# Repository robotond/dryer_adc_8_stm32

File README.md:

# dryer_adc_8_stm32
Dryer 8 input ADC board based on STM31G070CBT6

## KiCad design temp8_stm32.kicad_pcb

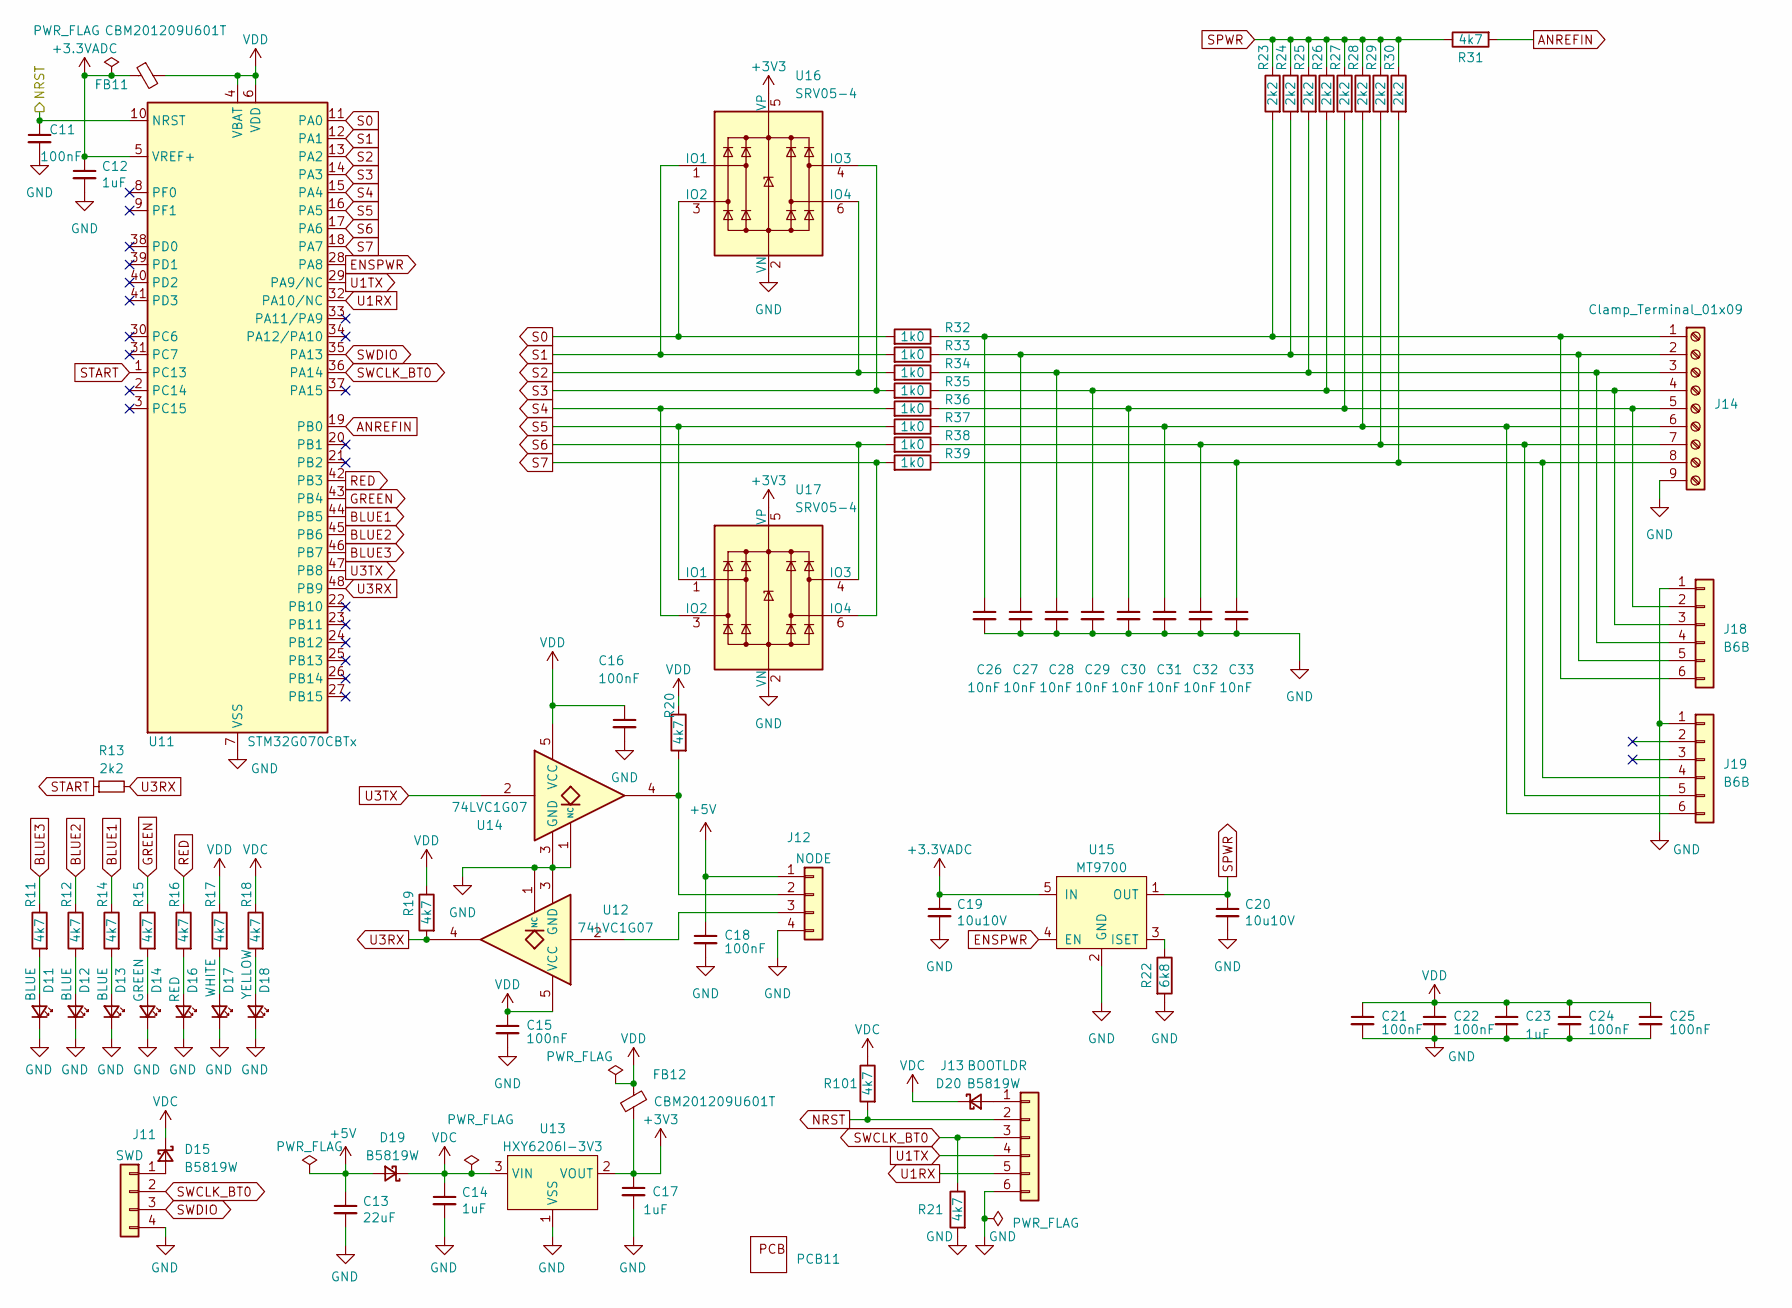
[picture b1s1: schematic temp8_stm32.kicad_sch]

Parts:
C11, C15, C16, C18, C21, C22, C24, C25: 100nF; C_0402_1005Metric; LCSC C1525
C12, C14, C17, C23: 1uF; C_0603_1608Metric; LCSC C15849
C13: 22uF; C_1206_3216Metric; LCSC C5672
C19, C20: 10u10V; C_0603_1608Metric; LCSC C19702
C26, C27, C28, C29, C30, C31, C32, C33: 10nF; C_0402_1005Metric; LCSC C15195
D11, D12, D13: BLUE; LED_0603_1608Metric; LCSC C72041
D14: GREEN; LED_0603_1608Metric; LCSC C72043
D15, D19, D20: B5819W; D_SOD-123; LCSC C8598
D16: RED; LED_0603_1608Metric; LCSC C2286
D17: WHITE; LED_0603_1608Metric; LCSC C2290
D18: YELLOW; LED_0603_1608Metric; LCSC C72038
FB11, FB12: CBM201209U601T; L_0805_2012Metric_Pad1.15x1.40mm_HandSolder; LCSC C139168
J11: SWD; JST_XH_B4B-XH-A_1x04_P2.50mm_Vertical; LCSC C144395
J12: NODE; JST_XH_B4B-XH-A_1x04_P2.50mm_Vertical; LCSC C144395
J13: BOOTLDR; JST_XH_B6B-XH-A_1x06_P2.50mm_Vertical; LCSC C144397
J14: Clamp_Terminal_01x09; DB141V-2.54-09P-C; LCSC C2898761
J18, J19: B6B; JST_XH_B6B-XH-A_1x06_P2.50mm_Vertical; LCSC C144397
PCB11: Dyer_ADC_78x28
R11, R12, R14, R15, R16, R17, R18, R19, R20, R21, R31, R101: 4k7; R_0402_1005Metric; LCSC C25900
R13, R23, R24, R25, R26, R27, R28, R29, R30: 2k2; R_0402_1005Metric; LCSC C517529
R22: 6k8; R_0402_1005Metric; LCSC C25917
R32, R33, R34, R35, R36, R37, R38, R39: 1k0; R_0402_1005Metric; LCSC C11702
U11: STM32G070CBTx; LQFP-48_7x7mm_P0.5mm; LCSC C529338
U12, U14: 74LVC1G07; SOT-23-5; LCSC C5124976
U13: HXY6206I-3V3; SOT-23; LCSC C5148688
U15: MT9700; SOT-23-5; LCSC C89855
U16, U17: SRV05-4; SOT-23-6; LCSC C2836319

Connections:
+3.3VADC: C12.1, C19.1, FB11.1, U11.5 (VREF+), U15.5 (IN)
+3V3: C17.1, FB12.2, U13.2 (VOUT), U16.5 (VP), U17.5 (VP)
+5V: C13.1, C18.1, D19.2 (A), J12.1
ANREFIN: R31.2, U11.19 (PB0)
BLUE1: R14.1, U11.44 (PB5)
BLUE2: R12.1, U11.45 (PB6)
BLUE3: R11.1, U11.46 (PB7)
ENSPWR: U11.28 (PA8), U15.4 (EN)
GND: C11.2, C12.2, C13.2, C14.2, C15.2, C16.2, C17.2, C18.2, C19.2, C20.2, C21.2, C22.2, C23.2, C24.2, C25.2, C26.2, C27.2, C28.2, C29.2, C30.2, C31.2, C32.2, C33.2, D11.1 (K), D12.1 (K), D13.1 (K), D14.1 (K), D16.1 (K), D17.1 (K), D18.1 (K), J11.4, J12.4, J13.6, J14.9, J18.1, J19.1, R21.2, R22.2, U11.7 (VSS), U12.1 (NC), U12.3 (GND), U13.1 (VSS), U14.1 (NC), U14.3 (GND), U15.2 (GND), U16.2 (VN), U17.2 (VN)
GREEN: R15.1, U11.43 (PB4)
NRST: C11.1, J13.2, R101.2, U11.10 (NRST)
unnamed: D11.2 (A), R11.2
unnamed: D12.2 (A), R12.2
unnamed: D13.2 (A), R14.2
unnamed: D14.2 (A), R15.2
unnamed: D15.2 (A), J11.1
unnamed: D16.2 (A), R16.2
unnamed: D17.2 (A), R17.2
unnamed: D18.2 (A), R18.2
unnamed: D20.2 (A), J13.1
unnamed: J12.2, R20.2, U14.4
unnamed: J12.3, U12.2
unnamed: C26.1, J14.1, J18.6, R23.2, R32.1
unnamed: C27.1, J14.2, J18.5, R24.2, R33.1
unnamed: C28.1, J14.3, J18.4, R25.2, R34.1
unnamed: C29.1, J14.4, J18.3, R26.2, R35.1
unnamed: C30.1, J14.5, J18.2, R27.2, R36.1
unnamed: C31.1, J14.6, J19.6, R28.2, R37.1
unnamed: C32.1, J14.7, J19.5, R29.2, R38.1
unnamed: C33.1, J14.8, J19.4, R30.2, R39.1
unnamed: R22.1, U15.3 (ISET)
RED: R16.1, U11.42 (PB3)
S0: R32.2, U11.11 (PA0), U16.3 (IO2)
S1: R33.2, U11.12 (PA1), U16.1 (IO1)
S2: R34.2, U11.13 (PA2), U16.6 (IO4)
S3: R35.2, U11.14 (PA3), U16.4 (IO3)
S4: R36.2, U11.15 (PA4), U17.3 (IO2)
S5: R37.2, U11.16 (PA5), U17.1 (IO1)
S6: R38.2, U11.17 (PA6), U17.4 (IO3)
S7: R39.2, U11.18 (PA7), U17.6 (IO4)
SPWR: C20.1, R23.1, R24.1, R25.1, R26.1, R27.1, R28.1, R29.1, R30.1, R31.1, U15.1 (OUT)
START: R13.1, U11.1 (PC13)
SWCLK_BT0: J11.2, J13.3, R21.1, U11.36 (PA14)
SWDIO: J11.3, U11.35 (PA13)
U1RX: J13.5, U11.32 (PA10/NC)
U1TX: J13.4, U11.29 (PA9/NC)
U3RX: R13.2, R19.2, U11.48 (PB9), U12.4
U3TX: U11.47 (PB8), U14.2
VDC: C14.1, D15.1 (K), D19.1 (K), D20.1 (K), R18.1, R101.1, U13.3 (VIN)
VDD: C15.1, C16.1, C21.1, C22.1, C23.1, C24.1, C25.1, FB11.2, FB12.1, R17.1, R19.1, R20.1, U11.4 (VBAT), U11.6 (VDD), U12.5 (VCC), U14.5 (VCC)

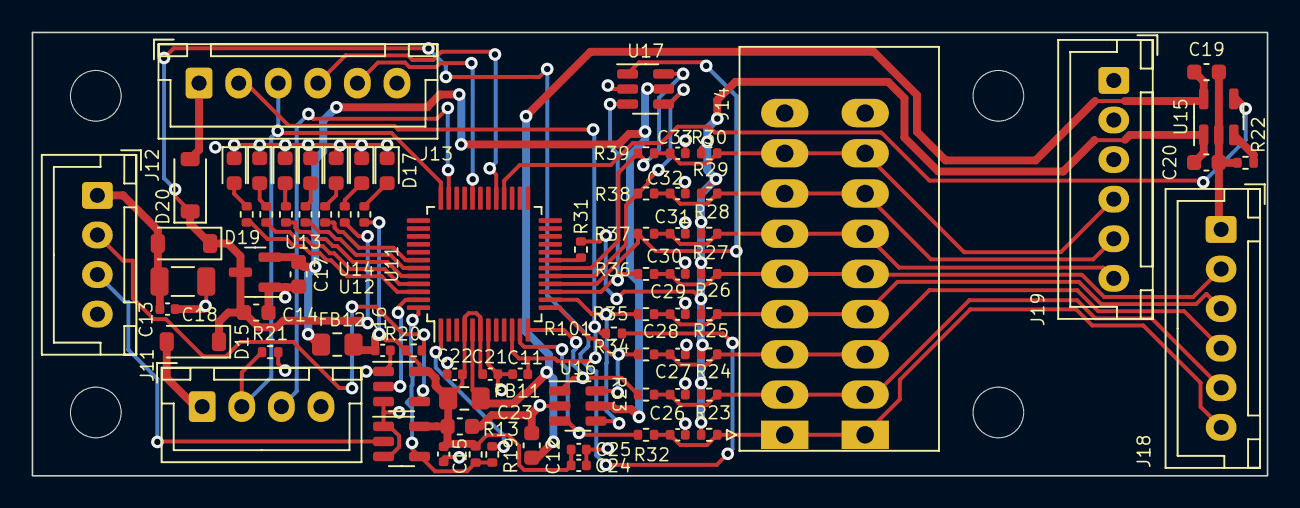
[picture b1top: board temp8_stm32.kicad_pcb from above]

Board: 2 copper layers, 78.0 x 28.0 mm, 79 parts (0 on the bottom side), 50 nets.

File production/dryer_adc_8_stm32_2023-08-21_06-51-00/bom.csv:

Designator,Footprint,Quantity,Value,LCSC Part #
"C11, C15, C16, C18, C21, C22, C24, C25",0402,8,100nF,
"C12, C14, C17, C23",0603,4,1uF,C15849
C13,1206,1,22uF,C5672
"C19, C20",0603,2,10u10V,C19702
"C26, C27, C28, C29, C30, C31, C32, C33",0402,8,10nF,
"D11, D12, D13",0603,3,BLUE,C72041
D14,0603,1,GREEN,C72043
"D15, D19, D20",D_SOD-123,3,B5819W,C8598
D16,0603,1,RED,C2286
D17,0603,1,WHITE,C2290
D18,0603,1,YELLOW,C72038
"FB11, FB12",0805,2,CBM201209U601T,C139168
J11,JST_XH_B4B-XH-A_1x04_P2.50mm_Vertical,1,SWD,C144395
J12,JST_XH_B4B-XH-A_1x04_P2.50mm_Vertical,1,NODE,C144395
J13,JST_XH_B6B-XH-A_1x06_P2.50mm_Vertical,1,BOOTLDR,C144397
J14,DB141V-2.54-09P-C,1,Clamp_Terminal_01x09,C2898761
"J18, J19",JST_XH_B6B-XH-A_1x06_P2.50mm_Vertical,2,B6B,C144397
PCB11,Dyer_ADC_78x28,1,~,
"R11, R12, R14, R15, R16, R17, R18, R19, R20, R21, R31",0402,11,4k7,
"R13, R23, R24, R25, R26, R27, R28, R29, R30",0402,9,2k2,
R22,0402,1,6k8,
"R32, R33, R34, R35, R36, R37, R38, R39",0402,8,1k0,
U11,LQFP-48_7x7mm_P0.5mm,1,STM32G070CBTx,C529338
"U12, U14",SOT-23-5,2,74LVC1G07,C5124976
U13,SOT-23,1,HXY6206I-3V3,C5148688
U15,SOT-23-5,1,MT9700,C89855
"U16, U17",SOT-23-6,2,SRV05-4,C2836319

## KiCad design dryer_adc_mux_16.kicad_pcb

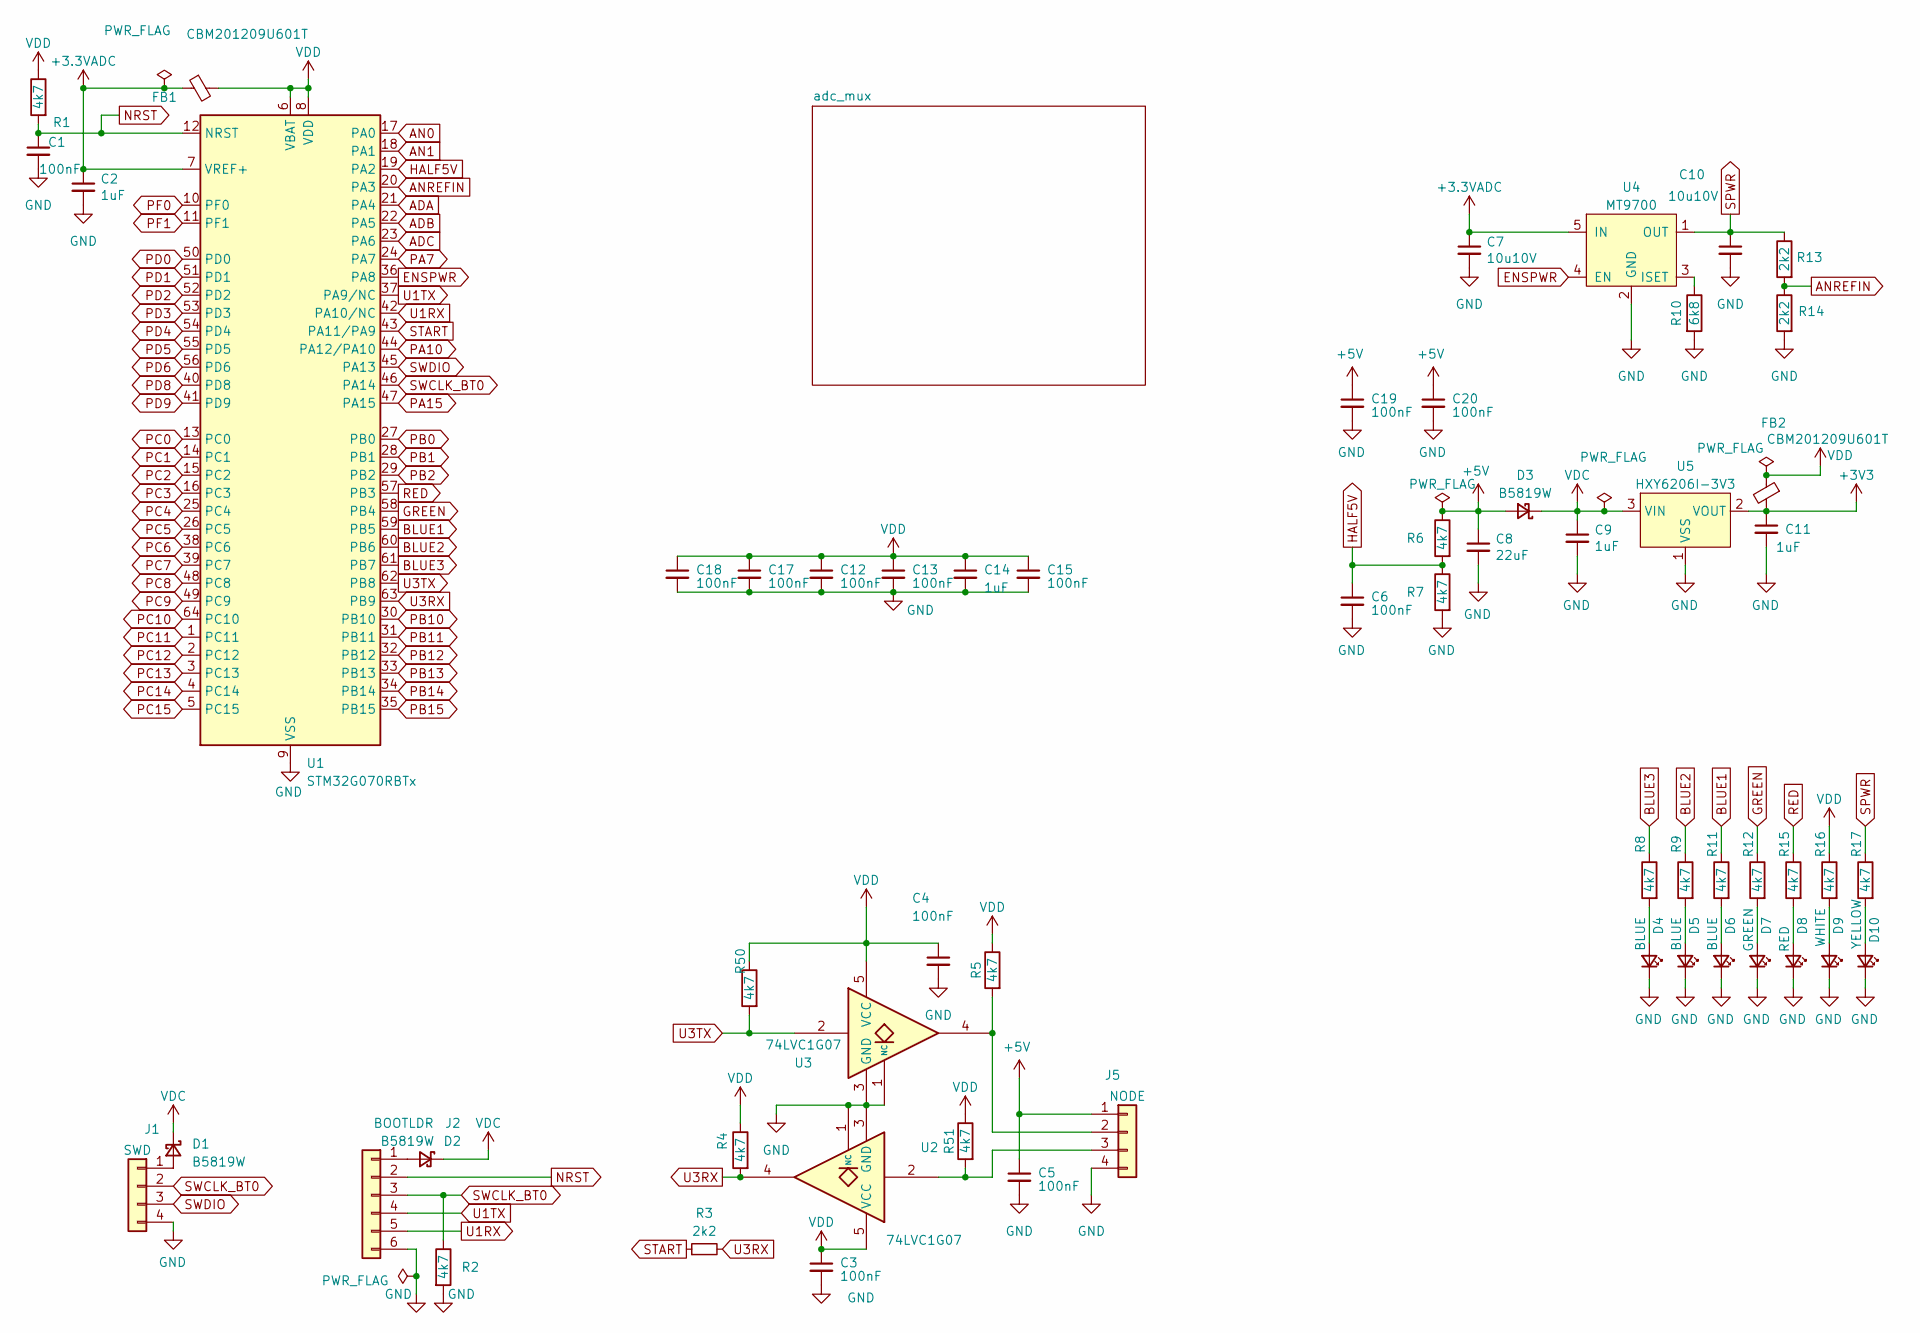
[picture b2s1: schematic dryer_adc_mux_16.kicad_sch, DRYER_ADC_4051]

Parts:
C1, C3, C4, C5, C6, C12, C13, C15, C17, C18, C19, C20: 100nF; C_0402_1005Metric; JLCPCB C1525
C2, C9, C11, C14: 1uF; C_0603_1608Metric; JLCPCB C15849
C7, C10: 10u10V; C_0603_1608Metric; JLCPCB C19702
C8: 22uF; C_1206_3216Metric; JLCPCB C5672
D1, D2, D3: B5819W; D_SOD-123; JLCPCB C8598
D4, D5, D6: BLUE; LED_0603_1608Metric; JLCPCB C72041
D7: GREEN; LED_0603_1608Metric; JLCPCB C72043
D8: RED; LED_0603_1608Metric; JLCPCB C2286
D9: WHITE; LED_0603_1608Metric; JLCPCB C2290
D10: YELLOW; LED_0603_1608Metric; JLCPCB C72038
FB1, FB2: CBM201209U601T; L_0805_2012Metric_Pad1.15x1.40mm_HandSolder; JLCPCB C139168
J1: SWD; JST_XH_B4B-XH-A_1x04_P2.50mm_Vertical; JLCPCB C144395
J2: BOOTLDR; JST_XH_B6B-XH-A_1x06_P2.50mm_Vertical; JLCPCB C144397
J5: NODE; JST_XH_B4B-XH-A_1x04_P2.50mm_Vertical; JLCPCB C144395
R1, R2, R4, R5, R6, R7, R8, R9, R11, R12, R15, R16, R17, R50, R51: 4k7; R_0402_1005Metric; JLCPCB C25900
R3, R13, R14: 2k2; R_0402_1005Metric; JLCPCB C517529
R10: 6k8; R_0402_1005Metric; JLCPCB C25917
U1: STM32G070RBTx; LQFP-64_10x10mm_P0.5mm; LCSC # C529340
U2, U3: 74LVC1G07; SOT-23-5; JLCPCB C5124976
U4: MT9700; SOT-23-5; JLCPCB C89855
U5: HXY6206I-3V3; SOT-23; JLCPCB C5148688

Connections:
+3.3VADC: C2.1, C7.1, FB1.1, U1.7 (VREF+), U4.5 (IN)
+3V3: C11.1, FB2.2, U5.2 (VOUT); also elsewhere on the board
+5V: C5.1, C8.1, C19.1, C20.1, D3.2 (A), J5.1, R6.1; also elsewhere on the board
ADA: U1.21 (PA4); also elsewhere on the board
ADB: U1.22 (PA5); also elsewhere on the board
ADC: U1.23 (PA6); also elsewhere on the board
AN0: U1.17 (PA0); also elsewhere on the board
AN1: U1.18 (PA1); also elsewhere on the board
ANREFIN: R13.2, R14.1, U1.20 (PA3)
BLUE1: R11.1, U1.59 (PB5)
BLUE2: R9.1, U1.60 (PB6)
BLUE3: R8.1, U1.61 (PB7)
ENSPWR: U1.36 (PA8), U4.4 (EN)
GND: C1.2, C2.2, C3.2, C4.2, C5.2, C6.2, C7.2, C8.2, C9.2, C10.2, C11.2, C12.2, C13.2, C14.2, C15.2, C17.2, C18.2, C19.2, C20.2, D4.1 (K), D5.1 (K), D6.1 (K), D7.1 (K), D8.1 (K), D9.1 (K), D10.1 (K), J1.4, J2.6, J5.4, R2.2, R7.2, R10.2, R14.2, U1.9 (VSS), U2.1 (NC), U2.3 (GND), U3.1 (NC), U3.3 (GND), U4.2 (GND), U5.1 (VSS); also elsewhere on the board
GREEN: R12.1, U1.58 (PB4)
HALF5V: C6.1, R6.2, R7.1, U1.19 (PA2)
NRST: C1.1, J2.2, R1.2, U1.12 (NRST)
unnamed: D1.2 (A), J1.1
unnamed: D2.2 (A), J2.1
unnamed: D4.2 (A), R8.2
unnamed: D5.2 (A), R9.2
unnamed: D6.2 (A), R11.2
unnamed: D7.2 (A), R12.2
unnamed: D8.2 (A), R15.2
unnamed: D9.2 (A), R16.2
unnamed: D10.2 (A), R17.2
unnamed: J5.2, R5.2, U3.4
unnamed: J5.3, R51.2, U2.2
unnamed: R10.1, U4.3 (ISET)
PB0: U1.27 (PB0)
PB1: U1.28 (PB1)
PB2: U1.29 (PB2)
PB10: U1.30 (PB10)
PB11: U1.31 (PB11)
PB12: U1.32 (PB12)
PB13: U1.33 (PB13)
PB14: U1.34 (PB14)
PB15: U1.35 (PB15)
PC0: U1.13 (PC0)
PC1: U1.14 (PC1)
PC2: U1.15 (PC2)
PC3: U1.16 (PC3)
PC4: U1.25 (PC4)
PC5: U1.26 (PC5)
PC6: U1.38 (PC6)
PC7: U1.39 (PC7)
PC8: U1.48 (PC8)
PC9: U1.49 (PC9)
PC10: U1.64 (PC10)
PC11: U1.1 (PC11)
PC12: U1.2 (PC12)
PC13: U1.3 (PC13)
PC14: U1.4 (PC14)
PC15: U1.5 (PC15)
PD0: U1.50 (PD0)
PD1: U1.51 (PD1)
PD2: U1.52 (PD2)
PD3: U1.53 (PD3)
PD4: U1.54 (PD4)
PD5: U1.55 (PD5)
PD6: U1.56 (PD6)
PD8: U1.40 (PD8)
PD9: U1.41 (PD9)
PF0: U1.10 (PF0)
PF1: U1.11 (PF1)
RED: R15.1, U1.57 (PB3)
SPWR: C10.1, R13.1, R17.1, U4.1 (OUT); also elsewhere on the board
START: R3.1, U1.43 (PA11/PA9)
SWCLK_BT0: J1.2, J2.3, R2.1, U1.46 (PA14)
SWDIO: J1.3, U1.45 (PA13)
U1RX: J2.5, U1.42 (PA10/NC)
U1TX: J2.4, U1.37 (PA9/NC)
U3RX: R3.2, R4.2, U1.63 (PB9), U2.4
U3TX: R50.2, U1.62 (PB8), U3.2
VDC: C9.1, D1.1 (K), D2.1 (K), D3.1 (K), U5.3 (VIN)
VDD: C3.1, C4.1, C12.1, C13.1, C14.1, C15.1, C17.1, C18.1, FB1.2, FB2.1, R1.1, R4.1, R5.1, R16.1, R50.1, R51.1, U1.6 (VBAT), U1.8 (VDD), U2.5 (VCC), U3.5 (VCC)

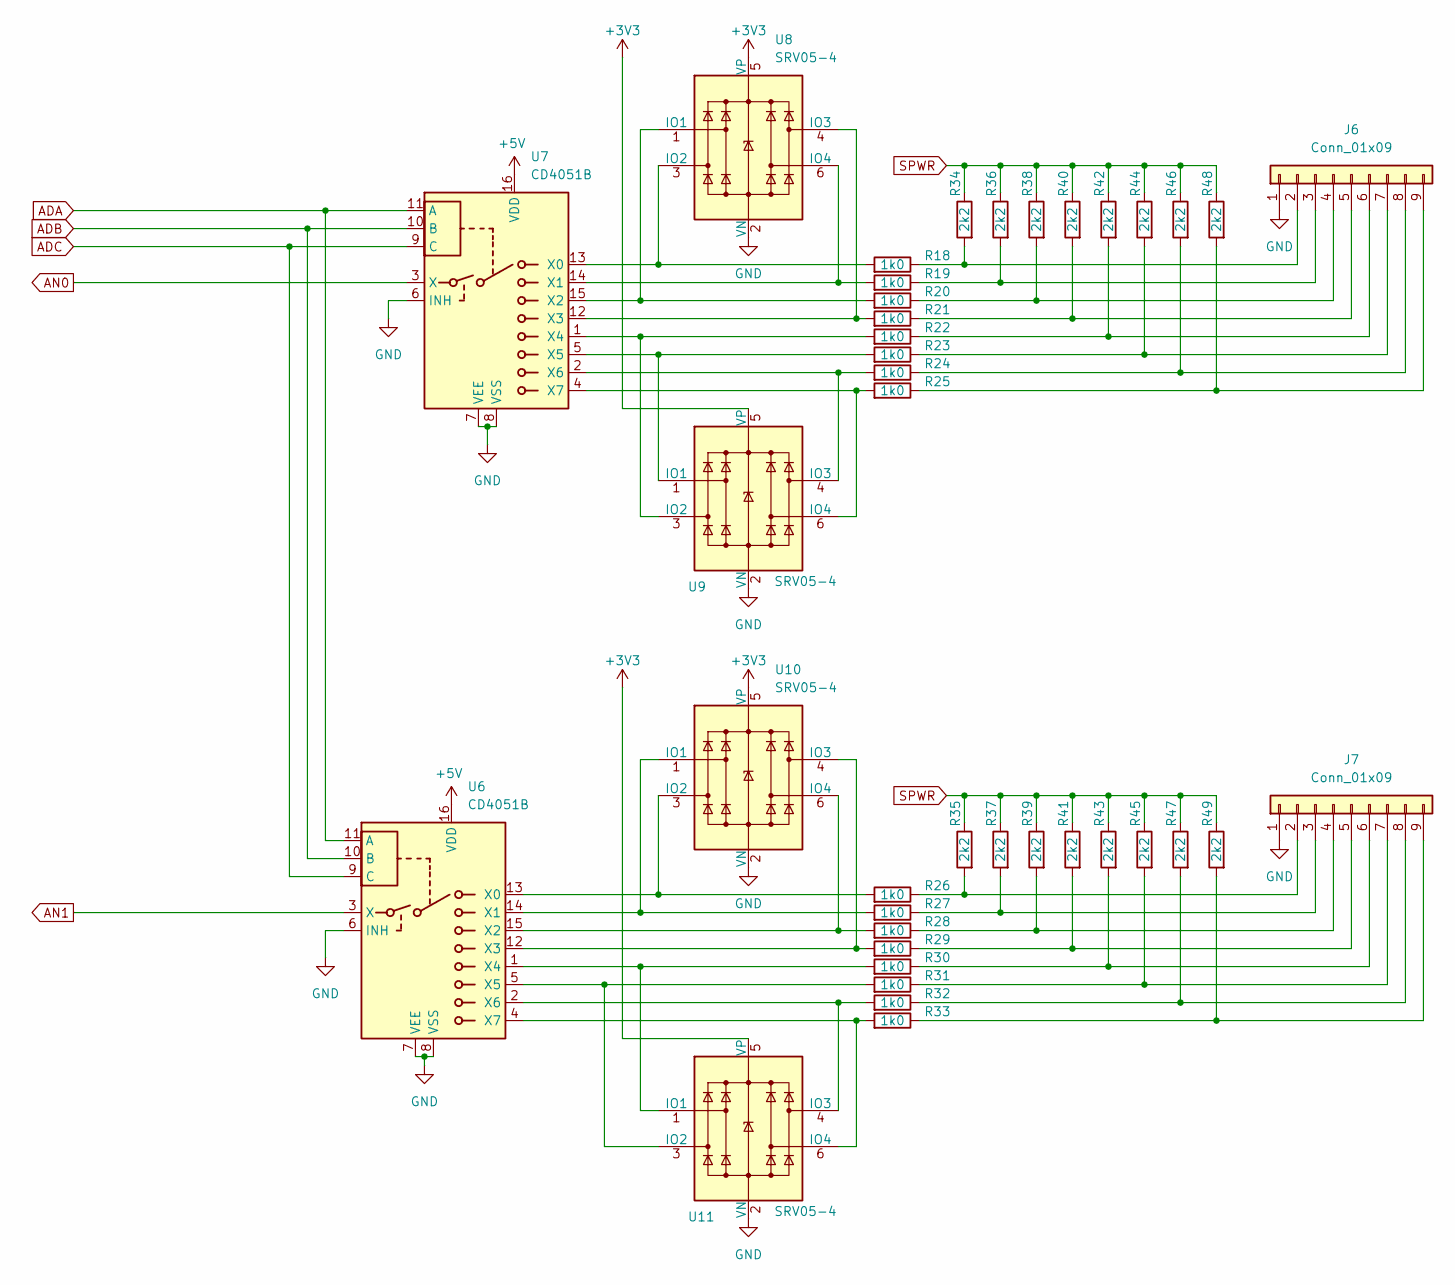
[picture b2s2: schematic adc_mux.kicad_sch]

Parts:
J6, J7: Conn_01x09; PinHeader_1x09_P2.54mm_Vertical
R18, R19, R20, R21, R22, R23, R24, R25, R26, R27, R28, R29, R30, R31, R32, R33: 1k0; R_0402_1005Metric; JLCPCB C11702
R34, R35, R36, R37, R38, R39, R40, R41, R42, R43, R44, R45, R46, R47, R48, R49: 2k2; R_0402_1005Metric; JLCPCB C517529
U6, U7: CD4051B; SOIC-16_3.9x9.9mm_P1.27mm; LCSC # C5645
U8, U9, U10, U11: SRV05-4; SOT-23-6; JLCPCB C2836319

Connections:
+3V3: U8.5 (VP), U9.5 (VP), U10.5 (VP), U11.5 (VP); also elsewhere on the board
+5V: U6.16 (VDD), U7.16 (VDD); also elsewhere on the board
ADA: U6.11 (A), U7.11 (A); also elsewhere on the board
ADB: U6.10 (B), U7.10 (B); also elsewhere on the board
ADC: U6.9 (C), U7.9 (C); also elsewhere on the board
AN0: U7.3 (X); also elsewhere on the board
AN1: U6.3 (X); also elsewhere on the board
GND: J6.1, J7.1, U6.6 (INH), U6.7 (VEE), U6.8 (VSS), U7.6 (INH), U7.7 (VEE), U7.8 (VSS), U8.2 (VN), U9.2 (VN), U10.2 (VN), U11.2 (VN); also elsewhere on the board
unnamed: J6.2, R18.1, R34.2
unnamed: J6.3, R19.1, R36.2
unnamed: J6.4, R20.1, R38.2
unnamed: J6.5, R21.1, R40.2
unnamed: J6.6, R22.1, R42.2
unnamed: J6.7, R23.1, R44.2
unnamed: J6.8, R24.1, R46.2
unnamed: J6.9, R25.1, R48.2
unnamed: J7.2, R26.1, R35.2
unnamed: J7.3, R27.1, R37.2
unnamed: J7.4, R28.1, R39.2
unnamed: J7.5, R29.1, R41.2
unnamed: J7.6, R30.1, R43.2
unnamed: J7.7, R31.1, R45.2
unnamed: J7.8, R32.1, R47.2
unnamed: J7.9, R33.1, R49.2
unnamed: R18.2, U7.13 (X0), U8.3 (IO2)
unnamed: R19.2, U7.14 (X1), U8.6 (IO4)
unnamed: R20.2, U7.15 (X2), U8.1 (IO1)
unnamed: R21.2, U7.12 (X3), U8.4 (IO3)
unnamed: R22.2, U7.1 (X4), U9.3 (IO2)
unnamed: R23.2, U7.5 (X5), U9.1 (IO1)
unnamed: R24.2, U7.2 (X6), U9.4 (IO3)
unnamed: R25.2, U7.4 (X7), U9.6 (IO4)
unnamed: R27.2, U6.14 (X1), U10.1 (IO1)
unnamed: R26.2, U6.13 (X0), U10.3 (IO2)
unnamed: R29.2, U6.12 (X3), U10.4 (IO3)
unnamed: R28.2, U6.15 (X2), U10.6 (IO4)
unnamed: R30.2, U6.1 (X4), U11.1 (IO1)
unnamed: R31.2, U6.5 (X5), U11.3 (IO2)
unnamed: R32.2, U6.2 (X6), U11.4 (IO3)
unnamed: R33.2, U6.4 (X7), U11.6 (IO4)
SPWR: R34.1, R35.1, R36.1, R37.1, R38.1, R39.1, R40.1, R41.1, R42.1, R43.1, R44.1, R45.1, R46.1, R47.1, R48.1, R49.1; also elsewhere on the board

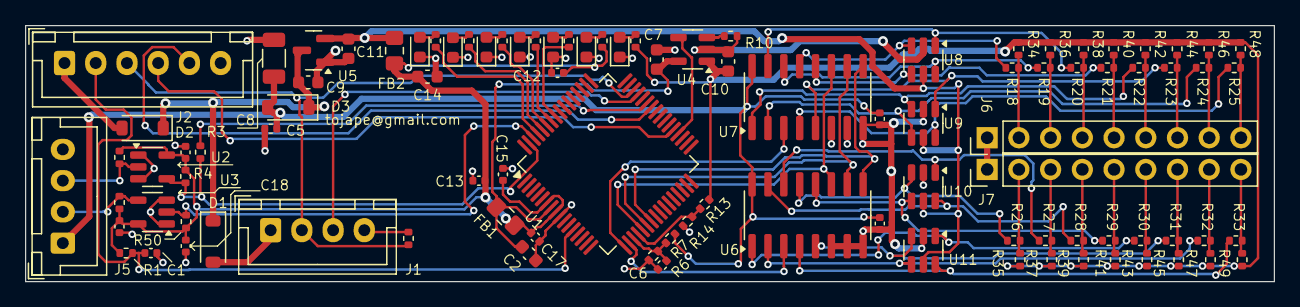
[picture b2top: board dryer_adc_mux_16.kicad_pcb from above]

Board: 2 copper layers, 100.0 x 20.5 mm, 98 parts (0 on the bottom side), 72 nets.

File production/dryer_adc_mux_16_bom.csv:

Designator,Footprint,Quantity,Value,LCSC Part #
"C1, C12, C13, C15, C17, C18, C19, C20, C3, C4, C5, C6",0402,12,100nF,
"C10, C7",0603,2,10u10V,
"C11, C14, C2, C9",0603,4,1uF,
C8,1206,1,22uF,
"D1, D2, D3",D_SOD-123,3,B5819W,
D10,0603,1,YELLOW,
"D4, D5, D6",0603,3,BLUE,
D7,0603,1,GREEN,
D8,0603,1,RED,
D9,0603,1,WHITE,
"FB1, FB2",0805,2,CBM201209U601T,
J1,JST_XH_B4B-XH-A_1x04_P2.50mm_Vertical,1,SWD,
J2,JST_XH_B6B-XH-A_1x06_P2.50mm_Vertical,1,BOOTLDR,
J5,JST_XH_B4B-XH-A_1x04_P2.50mm_Vertical,1,NODE,
"J6, J7",PinHeader_1x09_P2.54mm_Vertical,2,Conn_01x09,
"R1, R11, R12, R15, R16, R17, R2, R4, R5, R50, R51, R6, R7, R8, R9",0402,15,4k7,
R10,0402,1,6k8,
"R13, R14, R3, R34, R35, R36, R37, R38, R39, R40, R41, R42, R43, R44, R45, R46, R47, R48, R49",0402,19,2k2,
"R18, R19, R20, R21, R22, R23, R24, R25, R26, R27, R28, R29, R30, R31, R32, R33",0402,16,1k0,
U1,LQFP-64_10x10mm_P0.5mm,1,STM32G070RBTx,
"U10, U11, U8, U9",SOT-23-6,4,SRV05-4,
"U2, U3",SOT-23-5,2,74LVC1G07,
U4,SOT-23-5,1,MT9700,
U5,SOT-23,1,HXY6206I-3V3,
"U6, U7",SOIC-16_3.9x9.9mm_P1.27mm,2,CD4051B,

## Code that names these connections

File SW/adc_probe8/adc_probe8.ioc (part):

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Mcu.Name=STM32G070CBTx
Mcu.Package=LQFP48
Mcu.UserName=STM32G070CBTx
PA0.GPIOParameters=GPIO_Label
PA0.GPIO_Label=S0
PA0.Mode=IN0
PA0.Signal=ADC1_IN0
PA1.GPIOParameters=GPIO_Label
PA1.GPIO_Label=S1
PA1.Mode=IN1
PA1.Signal=ADC1_IN1
PA10.GPIOParameters=GPIO_Label
PA10.GPIO_Label=U1RX
PA10.Mode=Asynchronous
PA10.Signal=USART1_RX
PA13.GPIOParameters=GPIO_Label
PA13.GPIO_Label=SWDIO
PA13.Mode=Serial_Wire
PA13.Signal=SYS_SWDIO
PA14-BOOT0.GPIOParameters=GPIO_Label
PA14-BOOT0.GPIO_Label=SWCLK_BT0
PA14-BOOT0.Mode=Serial_Wire
PA14-BOOT0.Signal=SYS_SWCLK
PA2.GPIOParameters=GPIO_Label
PA2.GPIO_Label=S2
PA2.Mode=IN2
PA2.Signal=ADC1_IN2
PA3.GPIOParameters=GPIO_Label
PA3.GPIO_Label=S3
PA3.Mode=IN3
PA3.Signal=ADC1_IN3
PA4.GPIOParameters=GPIO_Label
PA4.GPIO_Label=S4
PA4.Mode=IN4
PA4.Signal=ADC1_IN4
PA5.GPIOParameters=GPIO_Label
PA5.GPIO_Label=S5
PA5.Mode=IN5
PA5.Signal=ADC1_IN5
PA6.GPIOParameters=GPIO_Label
PA6.GPIO_Label=S6
PA6.Mode=IN6
PA6.Signal=ADC1_IN6
PA7.GPIOParameters=GPIO_Label
PA7.GPIO_Label=S7
PA7.Mode=IN7
PA7.Signal=ADC1_IN7
PA8.GPIOParameters=GPIO_Label
PA8.GPIO_Label=ENSPWR
PA8.Signal=GPIO_Output
PA9.GPIOParameters=GPIO_Label
PA9.GPIO_Label=U1TX
PA9.Mode=Asynchronous
PA9.Signal=USART1_TX
PB0.GPIOParameters=GPIO_Label
PB0.GPIO_Label=AREFIN
PB0.Mode=IN8
PB0.Signal=ADC1_IN8
PB1.Signal=S_TIM3_CH4
PB3.GPIOParameters=GPIO_Label
PB3.GPIO_Label=RED
PB3.Signal=GPIO_Output
PB4.GPIOParameters=GPIO_Label
PB4.GPIO_Label=GREEN
PB4.Signal=GPIO_Output
PB5.GPIOParameters=GPIO_Label
PB5.GPIO_Label=BLUE1
PB5.Signal=GPIO_Output
PB6.GPIOParameters=GPIO_Label
PB6.GPIO_Label=BLUE2
PB6.Signal=GPIO_Output
PB7.GPIOParameters=GPIO_Label
PB7.GPIO_Label=BLUE3
PB7.Signal=GPIO_Output
PB8.GPIOParameters=GPIO_Label
PB8.GPIO_Label=U3TX
PB8.Mode=Asynchronous
PB8.Signal=USART3_TX
PB9.GPIOParameters=GPIO_Label
PB9.GPIO_Label=U3RX
PB9.Mode=Asynchronous
PB9.Signal=USART3_RX
PC13.GPIOParameters=GPIO_Label
PC13.GPIO_Label=START
PC13.Signal=GPIO_Input
RCC.HSE_VALUE=8000000
RCC.SYSCLKFreq_VALUE=64000000
RCC.SYSCLKSource=RCC_SYSCLKSOURCE_PLLCLK
board=custom

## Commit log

2023-08-21 ready to production
2023-09-02 ADC 8ch now works
2023-09-02 works with 8 sensors, temperatures seem OK
2023-09-03 After reset some delay added to handle sensor power rising slowly
2023-09-24 BPS set to 19200
2024-05-04 Schematics and layout ready to prototyping
2024-05-10 clock issue solved
2024-05-15 Baudrate 115200bps, 8 sensors
2024-05-16 .gitignore updated
2024-05-21 ADC offset corrected, raw data also sent to host
2024-05-22 unspecified changes

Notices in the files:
temp8_stm32.kicad_sch:
Public Domain
